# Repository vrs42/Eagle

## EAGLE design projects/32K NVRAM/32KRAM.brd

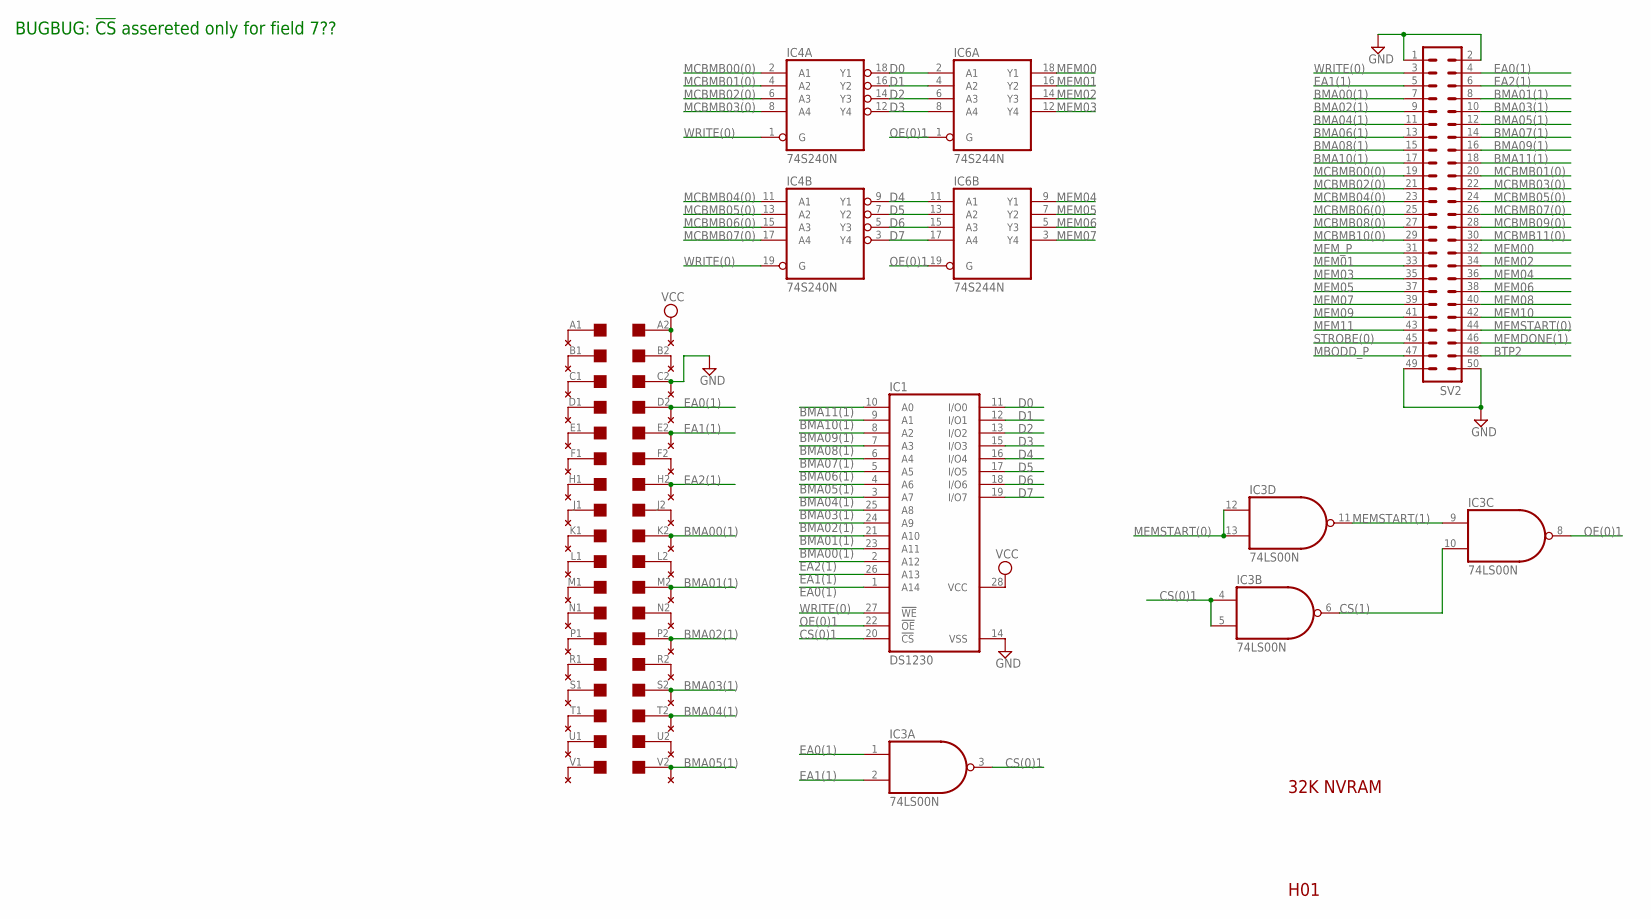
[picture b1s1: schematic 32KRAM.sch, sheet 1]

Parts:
EDGE1: EDGE-CON2
IC1: DS1230; DIL28-6
IC3: 74LS00N; DIL14
IC4: 74S240N; DIL20
IC6: 74S244N; DIL20
SV2: ML50L
U$1: THRU-HOLE2; THRU-HOLEB

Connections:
BMA00(1): EDGE1.K2, IC1.23 (A11), SV2.7, U$1.K2; also elsewhere on the board
BMA01(1): EDGE1.M2, IC1.21 (A10), SV2.8, U$1.M2; also elsewhere on the board
BMA02(1): EDGE1.P2, IC1.24 (A9), SV2.9, U$1.P2; also elsewhere on the board
BMA03(1): EDGE1.S2, IC1.25 (A8), SV2.10, U$1.S2; also elsewhere on the board
BMA04(1): EDGE1.T2, IC1.3 (A7), SV2.11, U$1.T2; also elsewhere on the board
BMA05(1): EDGE1.V2, IC1.4 (A6), SV2.12, U$1.V2; also elsewhere on the board
BMA06(1): IC1.5 (A5), SV2.13; also elsewhere on the board
BMA07(1): IC1.6 (A4), SV2.14; also elsewhere on the board
BMA08(1): IC1.7 (A3), SV2.15; also elsewhere on the board
BMA09(1): IC1.8 (A2), SV2.16; also elsewhere on the board
BMA10(1): IC1.9 (A1), SV2.17; also elsewhere on the board
BMA11(1): IC1.10 (A0), SV2.18; also elsewhere on the board
BTP2: SV2.48; also elsewhere on the board
CS(0)1: IC1.20 (!CS), IC3.3 (O), IC3.4 (I0), IC3.5 (I1)
CS(1): IC3.6 (O), IC3.10 (I1)
D0: IC1.11 (I/O0), IC4.18 (Y1), IC6.2 (A1)
D1: IC1.12 (I/O1), IC4.16 (Y2), IC6.4 (A2)
D2: IC1.13 (I/O2), IC4.14 (Y3), IC6.6 (A3)
D3: IC1.15 (I/O3), IC4.12 (Y4), IC6.8 (A4)
D4: IC1.16 (I/O4), IC4.9 (Y1), IC6.11 (A1)
D5: IC1.17 (I/O5), IC4.7 (Y2), IC6.13 (A2)
D6: IC1.18 (I/O6), IC4.5 (Y3), IC6.15 (A3)
D7: IC1.19 (I/O7), IC4.3 (Y4), IC6.17 (A4)
EA0(1): EDGE1.D2, IC1.1 (A14), IC3.1 (I0), SV2.4, U$1.D2; also elsewhere on the board
EA1(1): EDGE1.E2, IC1.26 (A13), IC3.2 (I1), SV2.5, U$1.E2; also elsewhere on the board
EA2(1): EDGE1.H2, IC1.2 (A12), SV2.6, U$1.H2; also elsewhere on the board
GND: EDGE1.C2, IC1.14 (VSS), IC3.7 (GND), IC4.10 (GND), IC6.10 (GND), SV2.1, SV2.2, SV2.49, SV2.50, U$1.C2; also elsewhere on the board
MBODD_P: SV2.47; also elsewhere on the board
MCBMB00(0): IC4.2 (A1), SV2.19; also elsewhere on the board
MCBMB01(0): IC4.4 (A2), SV2.20; also elsewhere on the board
MCBMB02(0): IC4.6 (A3), SV2.21; also elsewhere on the board
MCBMB03(0): IC4.8 (A4), SV2.22; also elsewhere on the board
MCBMB04(0): IC4.11 (A1), SV2.23; also elsewhere on the board
MCBMB05(0): IC4.13 (A2), SV2.24; also elsewhere on the board
MCBMB06(0): IC4.15 (A3), SV2.25; also elsewhere on the board
MCBMB07(0): IC4.17 (A4), SV2.26; also elsewhere on the board
MCBMB08(0): SV2.27; also elsewhere on the board
MCBMB09(0): SV2.28; also elsewhere on the board
MCBMB10(0): SV2.29; also elsewhere on the board
MCBMB11(0): SV2.30; also elsewhere on the board
MEM00: IC6.18 (Y1), SV2.32; also elsewhere on the board
MEM01: IC6.16 (Y2), SV2.33; also elsewhere on the board
MEM02: IC6.14 (Y3), SV2.34; also elsewhere on the board
MEM03: IC6.12 (Y4), SV2.35; also elsewhere on the board
MEM04: IC6.9 (Y1), SV2.36; also elsewhere on the board
MEM05: IC6.7 (Y2), SV2.37; also elsewhere on the board
MEM06: IC6.5 (Y3), SV2.38; also elsewhere on the board
MEM07: IC6.3 (Y4), SV2.39; also elsewhere on the board
MEM08: SV2.40; also elsewhere on the board
MEM09: SV2.41; also elsewhere on the board
MEM10: SV2.42; also elsewhere on the board
MEM11: SV2.43; also elsewhere on the board
MEMDONE(1): SV2.46; also elsewhere on the board
MEMSTART(0): IC3.12 (I0), IC3.13 (I1), SV2.44; also elsewhere on the board
MEMSTART(1): IC3.9 (I0), IC3.11 (O)
MEM_P: SV2.31; also elsewhere on the board
unnamed: EDGE1.L2, U$1.L2
unnamed: EDGE1.N2, U$1.N2
unnamed: EDGE1.R2, U$1.R2
unnamed: EDGE1.J2, U$1.J2
unnamed: EDGE1.F2, U$1.F2
unnamed: EDGE1.U2, U$1.U2
unnamed: EDGE1.B2, U$1.B2
unnamed: EDGE1.K1, U$1.K1
unnamed: EDGE1.L1, U$1.L1
unnamed: EDGE1.M1, U$1.M1
unnamed: EDGE1.N1, U$1.N1
unnamed: EDGE1.P1, U$1.P1
unnamed: EDGE1.R1, U$1.R1
unnamed: EDGE1.S1, U$1.S1
unnamed: EDGE1.T1, U$1.T1
unnamed: EDGE1.U1, U$1.U1
unnamed: EDGE1.V1, U$1.V1
unnamed: EDGE1.J1, U$1.J1
unnamed: EDGE1.H1, U$1.H1
unnamed: EDGE1.F1, U$1.F1
unnamed: EDGE1.E1, U$1.E1
unnamed: EDGE1.D1, U$1.D1
unnamed: EDGE1.C1, U$1.C1
unnamed: EDGE1.B1, U$1.B1
unnamed: EDGE1.A1, U$1.A1
OE(0)1: IC1.22 (!OE), IC3.8 (O), IC6.1 (G), IC6.19 (G)
STROBE(0): SV2.45; also elsewhere on the board
VCC: EDGE1.A2, IC1.28 (VCC), IC3.14 (VCC), IC4.20 (VCC), IC6.20 (VCC), U$1.A2; also elsewhere on the board
WRITE(0): IC1.27 (!WE), IC4.1 (G), IC4.19 (G), SV2.3; also elsewhere on the board

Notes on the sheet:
32K NVRAM
H01
BUGBUG: !CS! assereted only for field 7??

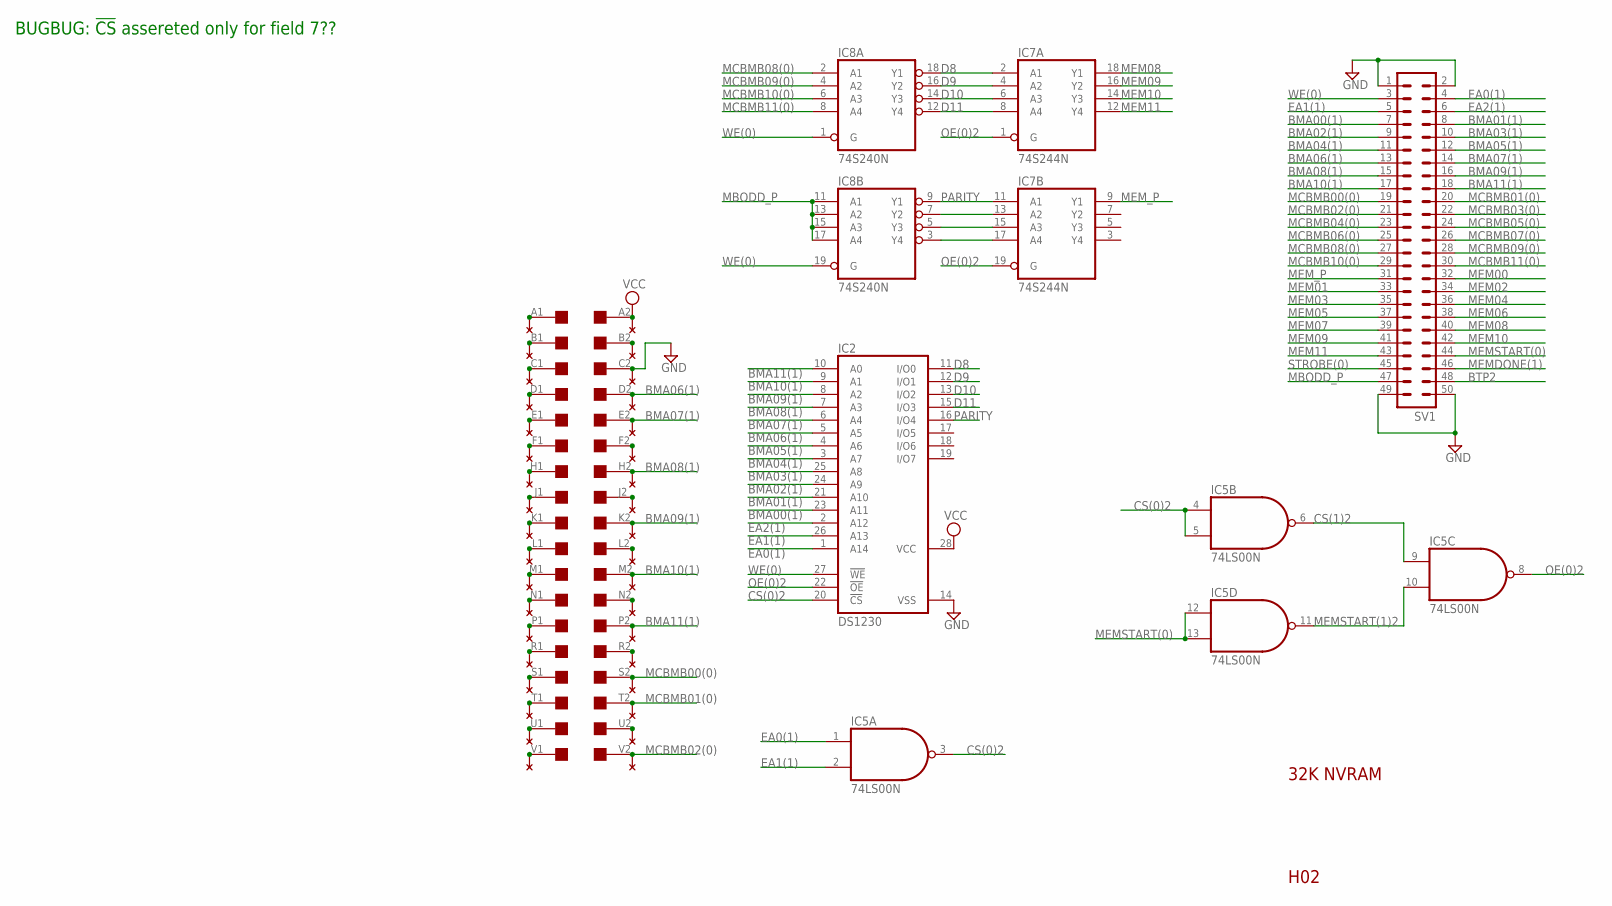
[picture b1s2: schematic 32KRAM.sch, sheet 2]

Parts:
EDGE2: EDGE-CON2
IC2: DS1230; DIL28-6
IC5: 74LS00N; DIL14
IC7: 74S244N; DIL20
IC8: 74S240N; DIL20
SV1: ML50L
U$2: THRU-HOLE2; THRU-HOLEB

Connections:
BMA00(1): IC2.23 (A11), SV1.7; also elsewhere on the board
BMA01(1): IC2.21 (A10), SV1.8; also elsewhere on the board
BMA02(1): IC2.24 (A9), SV1.9; also elsewhere on the board
BMA03(1): IC2.25 (A8), SV1.10; also elsewhere on the board
BMA04(1): IC2.3 (A7), SV1.11; also elsewhere on the board
BMA05(1): IC2.4 (A6), SV1.12; also elsewhere on the board
BMA06(1): EDGE2.D2, IC2.5 (A5), SV1.13, U$2.D2; also elsewhere on the board
BMA07(1): EDGE2.E2, IC2.6 (A4), SV1.14, U$2.E2; also elsewhere on the board
BMA08(1): EDGE2.H2, IC2.7 (A3), SV1.15, U$2.H2; also elsewhere on the board
BMA09(1): EDGE2.K2, IC2.8 (A2), SV1.16, U$2.K2; also elsewhere on the board
BMA10(1): EDGE2.M2, IC2.9 (A1), SV1.17, U$2.M2; also elsewhere on the board
BMA11(1): EDGE2.P2, IC2.10 (A0), SV1.18, U$2.P2; also elsewhere on the board
BTP2: SV1.48; also elsewhere on the board
CS(0)2: IC2.20 (!CS), IC5.3 (O), IC5.4 (I0), IC5.5 (I1)
CS(1)2: IC5.6 (O), IC5.9 (I0)
D8: IC2.11 (I/O0), IC7.2 (A1), IC8.18 (Y1)
D9: IC2.12 (I/O1), IC7.4 (A2), IC8.16 (Y2)
D10: IC2.13 (I/O2), IC7.6 (A3), IC8.14 (Y3)
D11: IC2.15 (I/O3), IC7.8 (A4), IC8.12 (Y4)
EA0(1): IC2.1 (A14), IC5.1 (I0), SV1.4; also elsewhere on the board
EA1(1): IC2.26 (A13), IC5.2 (I1), SV1.5; also elsewhere on the board
EA2(1): IC2.2 (A12), SV1.6; also elsewhere on the board
GND: EDGE2.C2, IC2.14 (VSS), IC5.7 (GND), IC7.10 (GND), IC8.10 (GND), SV1.1, SV1.2, SV1.49, SV1.50, U$2.C2; also elsewhere on the board
MBODD_P: IC8.11 (A1), IC8.13 (A2), IC8.15 (A3), IC8.17 (A4), SV1.47; also elsewhere on the board
MCBMB00(0): EDGE2.S2, SV1.19, U$2.S2; also elsewhere on the board
MCBMB01(0): EDGE2.T2, SV1.20, U$2.T2; also elsewhere on the board
MCBMB02(0): EDGE2.V2, SV1.21, U$2.V2; also elsewhere on the board
MCBMB03(0): SV1.22; also elsewhere on the board
MCBMB04(0): SV1.23; also elsewhere on the board
MCBMB05(0): SV1.24; also elsewhere on the board
MCBMB06(0): SV1.25; also elsewhere on the board
MCBMB07(0): SV1.26; also elsewhere on the board
MCBMB08(0): IC8.2 (A1), SV1.27; also elsewhere on the board
MCBMB09(0): IC8.4 (A2), SV1.28; also elsewhere on the board
MCBMB10(0): IC8.6 (A3), SV1.29; also elsewhere on the board
MCBMB11(0): IC8.8 (A4), SV1.30; also elsewhere on the board
MEM00: SV1.32; also elsewhere on the board
MEM01: SV1.33; also elsewhere on the board
MEM02: SV1.34; also elsewhere on the board
MEM03: SV1.35; also elsewhere on the board
MEM04: SV1.36; also elsewhere on the board
MEM05: SV1.37; also elsewhere on the board
MEM06: SV1.38; also elsewhere on the board
MEM07: SV1.39; also elsewhere on the board
MEM08: IC7.18 (Y1), SV1.40; also elsewhere on the board
MEM09: IC7.16 (Y2), SV1.41; also elsewhere on the board
MEM10: IC7.14 (Y3), SV1.42; also elsewhere on the board
MEM11: IC7.12 (Y4), SV1.43; also elsewhere on the board
MEMDONE(1): SV1.46; also elsewhere on the board
MEMSTART(0): IC5.12 (I0), IC5.13 (I1), SV1.44; also elsewhere on the board
MEMSTART(1)2: IC5.10 (I1), IC5.11 (O)
MEM_P: IC7.9 (Y1), SV1.31; also elsewhere on the board
unnamed: IC7.13 (A2), IC8.7 (Y2)
unnamed: IC7.15 (A3), IC8.5 (Y3)
unnamed: IC7.17 (A4), IC8.3 (Y4)
unnamed: EDGE2.L2, U$2.L2
unnamed: EDGE2.N2, U$2.N2
unnamed: EDGE2.R2, U$2.R2
unnamed: EDGE2.J2, U$2.J2
unnamed: EDGE2.F2, U$2.F2
unnamed: EDGE2.U2, U$2.U2
unnamed: EDGE2.B2, U$2.B2
unnamed: EDGE2.K1, U$2.K1
unnamed: EDGE2.L1, U$2.L1
unnamed: EDGE2.M1, U$2.M1
unnamed: EDGE2.N1, U$2.N1
unnamed: EDGE2.P1, U$2.P1
unnamed: EDGE2.R1, U$2.R1
unnamed: EDGE2.S1, U$2.S1
unnamed: EDGE2.T1, U$2.T1
unnamed: EDGE2.U1, U$2.U1
unnamed: EDGE2.V1, U$2.V1
unnamed: EDGE2.J1, U$2.J1
unnamed: EDGE2.H1, U$2.H1
unnamed: EDGE2.F1, U$2.F1
unnamed: EDGE2.E1, U$2.E1
unnamed: EDGE2.D1, U$2.D1
unnamed: EDGE2.C1, U$2.C1
unnamed: EDGE2.B1, U$2.B1
unnamed: EDGE2.A1, U$2.A1
OE(0)2: IC2.22 (!OE), IC5.8 (O), IC7.1 (G), IC7.19 (G)
PARITY: IC2.16 (I/O4), IC7.11 (A1), IC8.9 (Y1)
STROBE(0): SV1.45; also elsewhere on the board
VCC: EDGE2.A2, IC2.28 (VCC), IC5.14 (VCC), IC7.20 (VCC), IC8.20 (VCC), U$2.A2; also elsewhere on the board
WE(0): IC2.27 (!WE), IC8.1 (G), IC8.19 (G), SV1.3; also elsewhere on the board

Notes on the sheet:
32K NVRAM
H02
BUGBUG: !CS! assereted only for field 7??

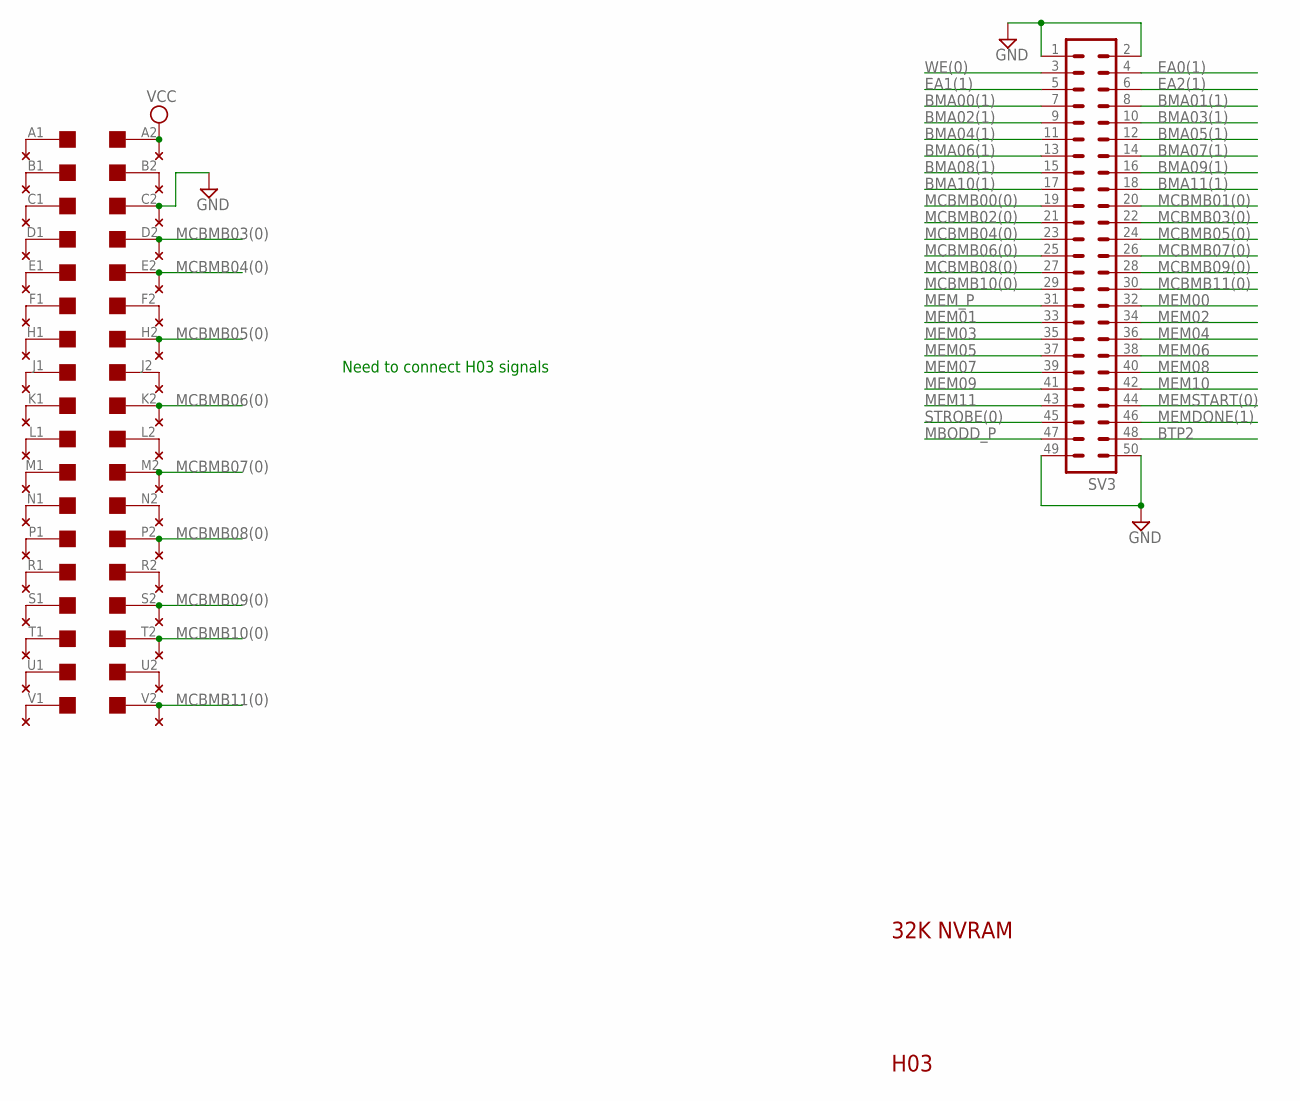
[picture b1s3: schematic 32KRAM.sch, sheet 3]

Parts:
EDGE3: EDGE-CON2
SV3: ML50L
U$3: THRU-HOLE2; THRU-HOLEB

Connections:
BMA00(1): SV3.7; also elsewhere on the board
BMA01(1): SV3.8; also elsewhere on the board
BMA02(1): SV3.9; also elsewhere on the board
BMA03(1): SV3.10; also elsewhere on the board
BMA04(1): SV3.11; also elsewhere on the board
BMA05(1): SV3.12; also elsewhere on the board
BMA06(1): SV3.13; also elsewhere on the board
BMA07(1): SV3.14; also elsewhere on the board
BMA08(1): SV3.15; also elsewhere on the board
BMA09(1): SV3.16; also elsewhere on the board
BMA10(1): SV3.17; also elsewhere on the board
BMA11(1): SV3.18; also elsewhere on the board
BTP2: SV3.48; also elsewhere on the board
EA0(1): SV3.4; also elsewhere on the board
EA1(1): SV3.5; also elsewhere on the board
EA2(1): SV3.6; also elsewhere on the board
GND: EDGE3.C2, SV3.1, SV3.2, SV3.49, SV3.50, U$3.C2; also elsewhere on the board
MBODD_P: SV3.47; also elsewhere on the board
MCBMB00(0): SV3.19; also elsewhere on the board
MCBMB01(0): SV3.20; also elsewhere on the board
MCBMB02(0): SV3.21; also elsewhere on the board
MCBMB03(0): EDGE3.D2, SV3.22, U$3.D2; also elsewhere on the board
MCBMB04(0): EDGE3.E2, SV3.23, U$3.E2; also elsewhere on the board
MCBMB05(0): EDGE3.H2, SV3.24, U$3.H2; also elsewhere on the board
MCBMB06(0): EDGE3.K2, SV3.25, U$3.K2; also elsewhere on the board
MCBMB07(0): EDGE3.M2, SV3.26, U$3.M2; also elsewhere on the board
MCBMB08(0): EDGE3.P2, SV3.27, U$3.P2; also elsewhere on the board
MCBMB09(0): EDGE3.S2, SV3.28, U$3.S2; also elsewhere on the board
MCBMB10(0): EDGE3.T2, SV3.29, U$3.T2; also elsewhere on the board
MCBMB11(0): EDGE3.V2, SV3.30, U$3.V2; also elsewhere on the board
MEM00: SV3.32; also elsewhere on the board
MEM01: SV3.33; also elsewhere on the board
MEM02: SV3.34; also elsewhere on the board
MEM03: SV3.35; also elsewhere on the board
MEM04: SV3.36; also elsewhere on the board
MEM05: SV3.37; also elsewhere on the board
MEM06: SV3.38; also elsewhere on the board
MEM07: SV3.39; also elsewhere on the board
MEM08: SV3.40; also elsewhere on the board
MEM09: SV3.41; also elsewhere on the board
MEM10: SV3.42; also elsewhere on the board
MEM11: SV3.43; also elsewhere on the board
MEMDONE(1): SV3.46; also elsewhere on the board
MEMSTART(0): SV3.44; also elsewhere on the board
MEM_P: SV3.31; also elsewhere on the board
unnamed: EDGE3.J2, U$3.J2
unnamed: EDGE3.L2, U$3.L2
unnamed: EDGE3.N2, U$3.N2
unnamed: EDGE3.F2, U$3.F2
unnamed: EDGE3.R2, U$3.R2
unnamed: EDGE3.B2, U$3.B2
unnamed: EDGE3.U2, U$3.U2
unnamed: EDGE3.A1, U$3.A1
unnamed: EDGE3.V1, U$3.V1
unnamed: EDGE3.U1, U$3.U1
unnamed: EDGE3.T1, U$3.T1
unnamed: EDGE3.S1, U$3.S1
unnamed: EDGE3.R1, U$3.R1
unnamed: EDGE3.P1, U$3.P1
unnamed: EDGE3.N1, U$3.N1
unnamed: EDGE3.M1, U$3.M1
unnamed: EDGE3.L1, U$3.L1
unnamed: EDGE3.K1, U$3.K1
unnamed: EDGE3.J1, U$3.J1
unnamed: EDGE3.H1, U$3.H1
unnamed: EDGE3.F1, U$3.F1
unnamed: EDGE3.E1, U$3.E1
unnamed: EDGE3.D1, U$3.D1
unnamed: EDGE3.C1, U$3.C1
unnamed: EDGE3.B1, U$3.B1
STROBE(0): SV3.45; also elsewhere on the board
VCC: EDGE3.A2, U$3.A2; also elsewhere on the board
WE(0): SV3.3; also elsewhere on the board

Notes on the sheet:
32K NVRAM
H03
Need to connect H03 signals

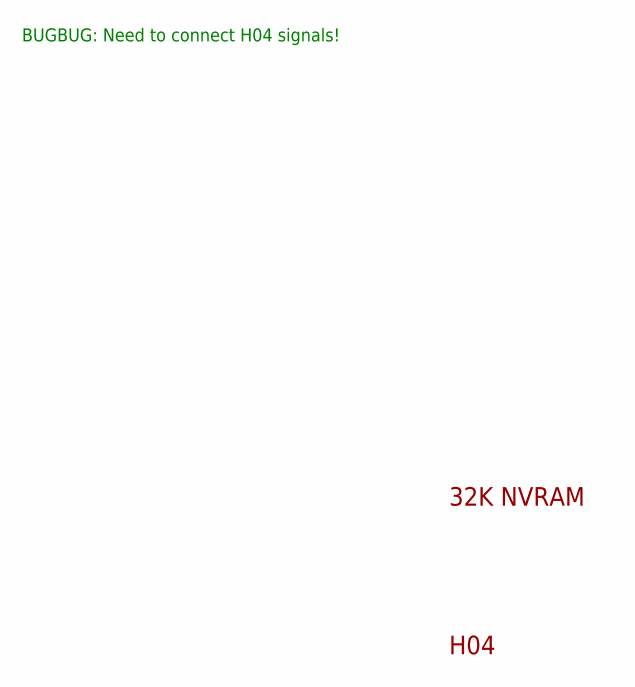
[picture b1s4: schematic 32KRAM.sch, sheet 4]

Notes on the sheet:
32K NVRAM
H04
BUGBUG: Need to connect H04 signals!

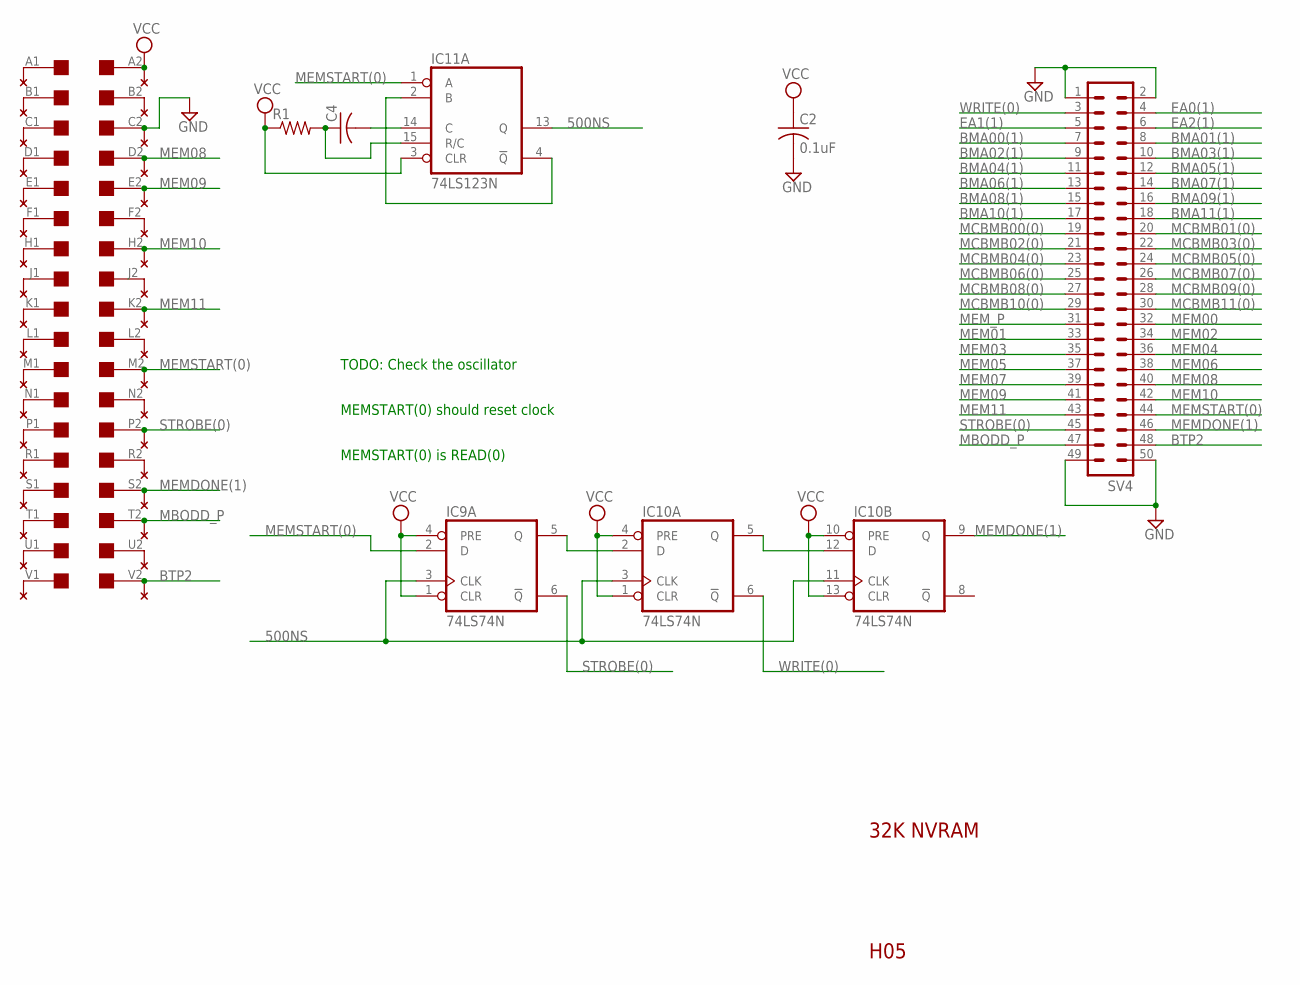
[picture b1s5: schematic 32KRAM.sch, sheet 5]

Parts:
C2: 0.1uF; C050-025X075
C4: C-US050-025X075; C050-025X075
EDGE5: EDGE-CON2
IC9, IC10: 74LS74N; DIL14
IC11: 74LS123N; DIL16
R1: R-US_0309/10; 0309/10
SV4: ML50L
U$5: THRU-HOLE2; THRU-HOLEB

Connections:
500NS: IC9.3 (CLK), IC10.3 (CLK), IC10.11 (CLK), IC11.13 (Q)
BMA00(1): SV4.7; also elsewhere on the board
BMA01(1): SV4.8; also elsewhere on the board
BMA02(1): SV4.9; also elsewhere on the board
BMA03(1): SV4.10; also elsewhere on the board
BMA04(1): SV4.11; also elsewhere on the board
BMA05(1): SV4.12; also elsewhere on the board
BMA06(1): SV4.13; also elsewhere on the board
BMA07(1): SV4.14; also elsewhere on the board
BMA08(1): SV4.15; also elsewhere on the board
BMA09(1): SV4.16; also elsewhere on the board
BMA10(1): SV4.17; also elsewhere on the board
BMA11(1): SV4.18; also elsewhere on the board
BTP2: EDGE5.V2, SV4.48, U$5.V2; also elsewhere on the board
EA0(1): SV4.4; also elsewhere on the board
EA1(1): SV4.5; also elsewhere on the board
EA2(1): SV4.6; also elsewhere on the board
GND: C2.2, EDGE5.C2, IC9.7 (GND), IC10.7 (GND), IC11.8 (GND), SV4.1, SV4.2, SV4.49, SV4.50, U$5.C2; also elsewhere on the board
MBODD_P: EDGE5.T2, SV4.47, U$5.T2; also elsewhere on the board
MCBMB00(0): SV4.19; also elsewhere on the board
MCBMB01(0): SV4.20; also elsewhere on the board
MCBMB02(0): SV4.21; also elsewhere on the board
MCBMB03(0): SV4.22; also elsewhere on the board
MCBMB04(0): SV4.23; also elsewhere on the board
MCBMB05(0): SV4.24; also elsewhere on the board
MCBMB06(0): SV4.25; also elsewhere on the board
MCBMB07(0): SV4.26; also elsewhere on the board
MCBMB08(0): SV4.27; also elsewhere on the board
MCBMB09(0): SV4.28; also elsewhere on the board
MCBMB10(0): SV4.29; also elsewhere on the board
MCBMB11(0): SV4.30; also elsewhere on the board
MEM00: SV4.32; also elsewhere on the board
MEM01: SV4.33; also elsewhere on the board
MEM02: SV4.34; also elsewhere on the board
MEM03: SV4.35; also elsewhere on the board
MEM04: SV4.36; also elsewhere on the board
MEM05: SV4.37; also elsewhere on the board
MEM06: SV4.38; also elsewhere on the board
MEM07: SV4.39; also elsewhere on the board
MEM08: EDGE5.D2, SV4.40, U$5.D2; also elsewhere on the board
MEM09: EDGE5.E2, SV4.41, U$5.E2; also elsewhere on the board
MEM10: EDGE5.H2, SV4.42, U$5.H2; also elsewhere on the board
MEM11: EDGE5.K2, SV4.43, U$5.K2; also elsewhere on the board
MEMDONE(1): EDGE5.S2, IC10.9 (Q), SV4.46, U$5.S2; also elsewhere on the board
MEMSTART(0): EDGE5.M2, IC9.2 (D), IC11.1 (A), SV4.44, U$5.M2; also elsewhere on the board
MEM_P: SV4.31; also elsewhere on the board
unnamed: IC9.5 (Q), IC10.2 (D)
unnamed: IC10.5 (Q), IC10.12 (D)
unnamed: IC11.2 (B), IC11.4 (!Q)
unnamed: C4.2, IC11.14 (C)
unnamed: C4.1, IC11.15 (R/C), R1.2
unnamed: EDGE5.J2, U$5.J2
unnamed: EDGE5.L2, U$5.L2
unnamed: EDGE5.N2, U$5.N2
unnamed: EDGE5.F2, U$5.F2
unnamed: EDGE5.R2, U$5.R2
unnamed: EDGE5.B2, U$5.B2
unnamed: EDGE5.U2, U$5.U2
unnamed: EDGE5.A1, U$5.A1
unnamed: EDGE5.V1, U$5.V1
unnamed: EDGE5.U1, U$5.U1
unnamed: EDGE5.T1, U$5.T1
unnamed: EDGE5.S1, U$5.S1
unnamed: EDGE5.R1, U$5.R1
unnamed: EDGE5.P1, U$5.P1
unnamed: EDGE5.N1, U$5.N1
unnamed: EDGE5.M1, U$5.M1
unnamed: EDGE5.L1, U$5.L1
unnamed: EDGE5.K1, U$5.K1
unnamed: EDGE5.J1, U$5.J1
unnamed: EDGE5.H1, U$5.H1
unnamed: EDGE5.F1, U$5.F1
unnamed: EDGE5.E1, U$5.E1
unnamed: EDGE5.D1, U$5.D1
unnamed: EDGE5.C1, U$5.C1
unnamed: EDGE5.B1, U$5.B1
STROBE(0): EDGE5.P2, IC9.6 (!Q), SV4.45, U$5.P2; also elsewhere on the board
VCC: C2.1, EDGE5.A2, IC9.1 (CLR), IC9.4 (PRE), IC9.14 (VCC), IC10.1 (CLR), IC10.4 (PRE), IC10.10 (PRE), IC10.13 (CLR), IC10.14 (VCC), IC11.3 (CLR), IC11.16 (VCC), R1.1, U$5.A2; also elsewhere on the board
WRITE(0): IC10.6 (!Q), SV4.3; also elsewhere on the board

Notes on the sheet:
32K NVRAM
H05
TODO: Check the oscillator
MEMSTART(0) is READ(0)
MEMSTART(0) should reset clock

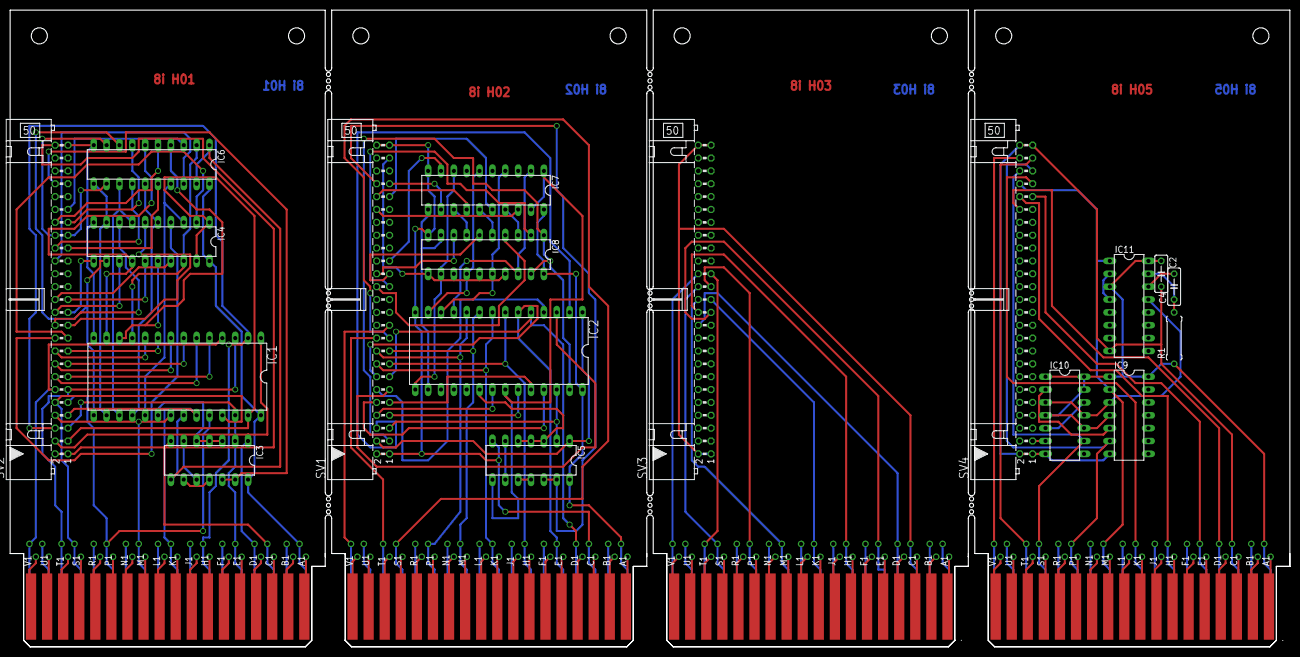
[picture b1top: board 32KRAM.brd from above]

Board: 2 copper layers, 252.7 x 125.7 mm, 27 parts (0 on the bottom side), 179 nets.

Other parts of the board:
E$1: DECPROTO1111

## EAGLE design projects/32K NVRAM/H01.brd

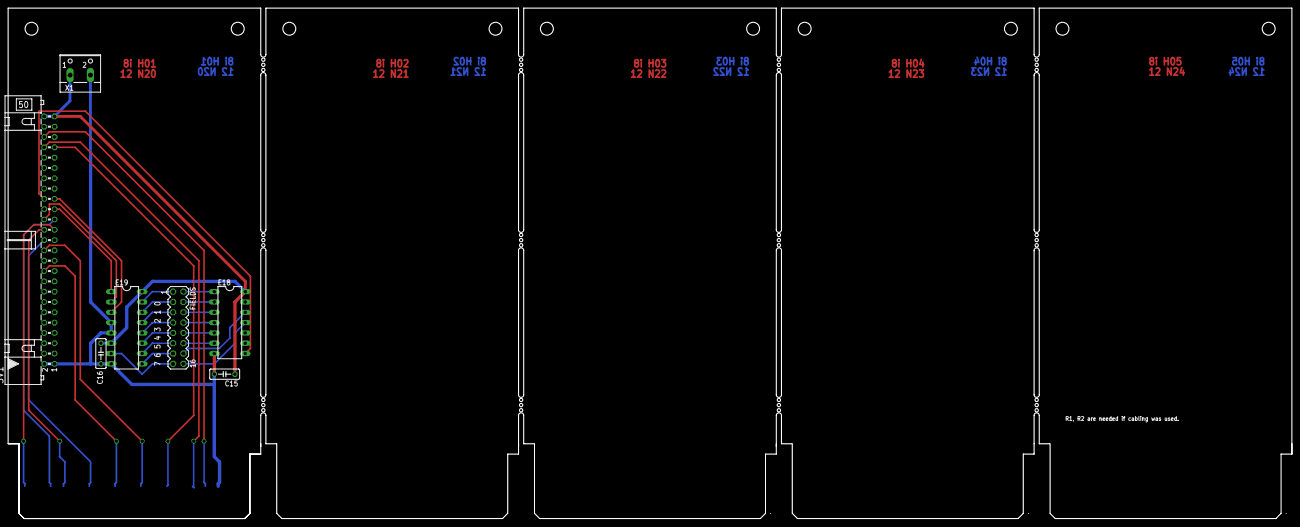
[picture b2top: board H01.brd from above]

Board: 2 copper layers, 316.2 x 125.7 mm, 9 parts (0 on the bottom side), 31 nets.

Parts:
C15, C16: 0.1uF; C050-025X075
E18: 74LS30N; DIL14
E19: 74LS138N; DIL16
FIELDS: MA08-2
H01: EDGE-CON1
SV1: ML50L
U$6: DECPROTO11111
X1: POWER; W237-102

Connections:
BMA00(1): H01.K2, SV1.24
BMA01(1): H01.M2, SV1.20
BMA02(1): H01.P2, SV1.26
BMA03(1): H01.S2, SV1.28
BMA04(1): H01.T2, SV1.29
BMA05(1): H01.V2, SV1.27
EA0(1): E19.3, SV1.33
EA1(1): E19.2, SV1.30
EA2(1): E19.1, SV1.31
FS(1): E18.8, SV1.34
GND: C15.2, C16.2, E18.7, E19.4, E19.5, E19.8, H01.C2, SV1.1, SV1.2, X1.2
MCBMB03(0): H01.D2, SV1.46
MCBMB04(0): H01.E2, SV1.44
MCBMB05(0): H01.H2, SV1.43
unnamed: E19.15, FIELDS.1
unnamed: E19.14, FIELDS.3
unnamed: E19.13, FIELDS.5
unnamed: E19.12, FIELDS.7
unnamed: E19.11, FIELDS.9
unnamed: E19.10, FIELDS.11
unnamed: E19.9, FIELDS.13
unnamed: E19.7, FIELDS.15
unnamed: E18.4, FIELDS.8
unnamed: E18.3, FIELDS.6
unnamed: E18.2, FIELDS.4
unnamed: E18.1, FIELDS.2
unnamed: E18.5, FIELDS.10
unnamed: E18.6, FIELDS.12
unnamed: E18.12, FIELDS.14
unnamed: E18.11, FIELDS.16
VCC: C15.1, C16.1, E18.14, E19.6, E19.16, SV1.49, SV1.50, X1.1

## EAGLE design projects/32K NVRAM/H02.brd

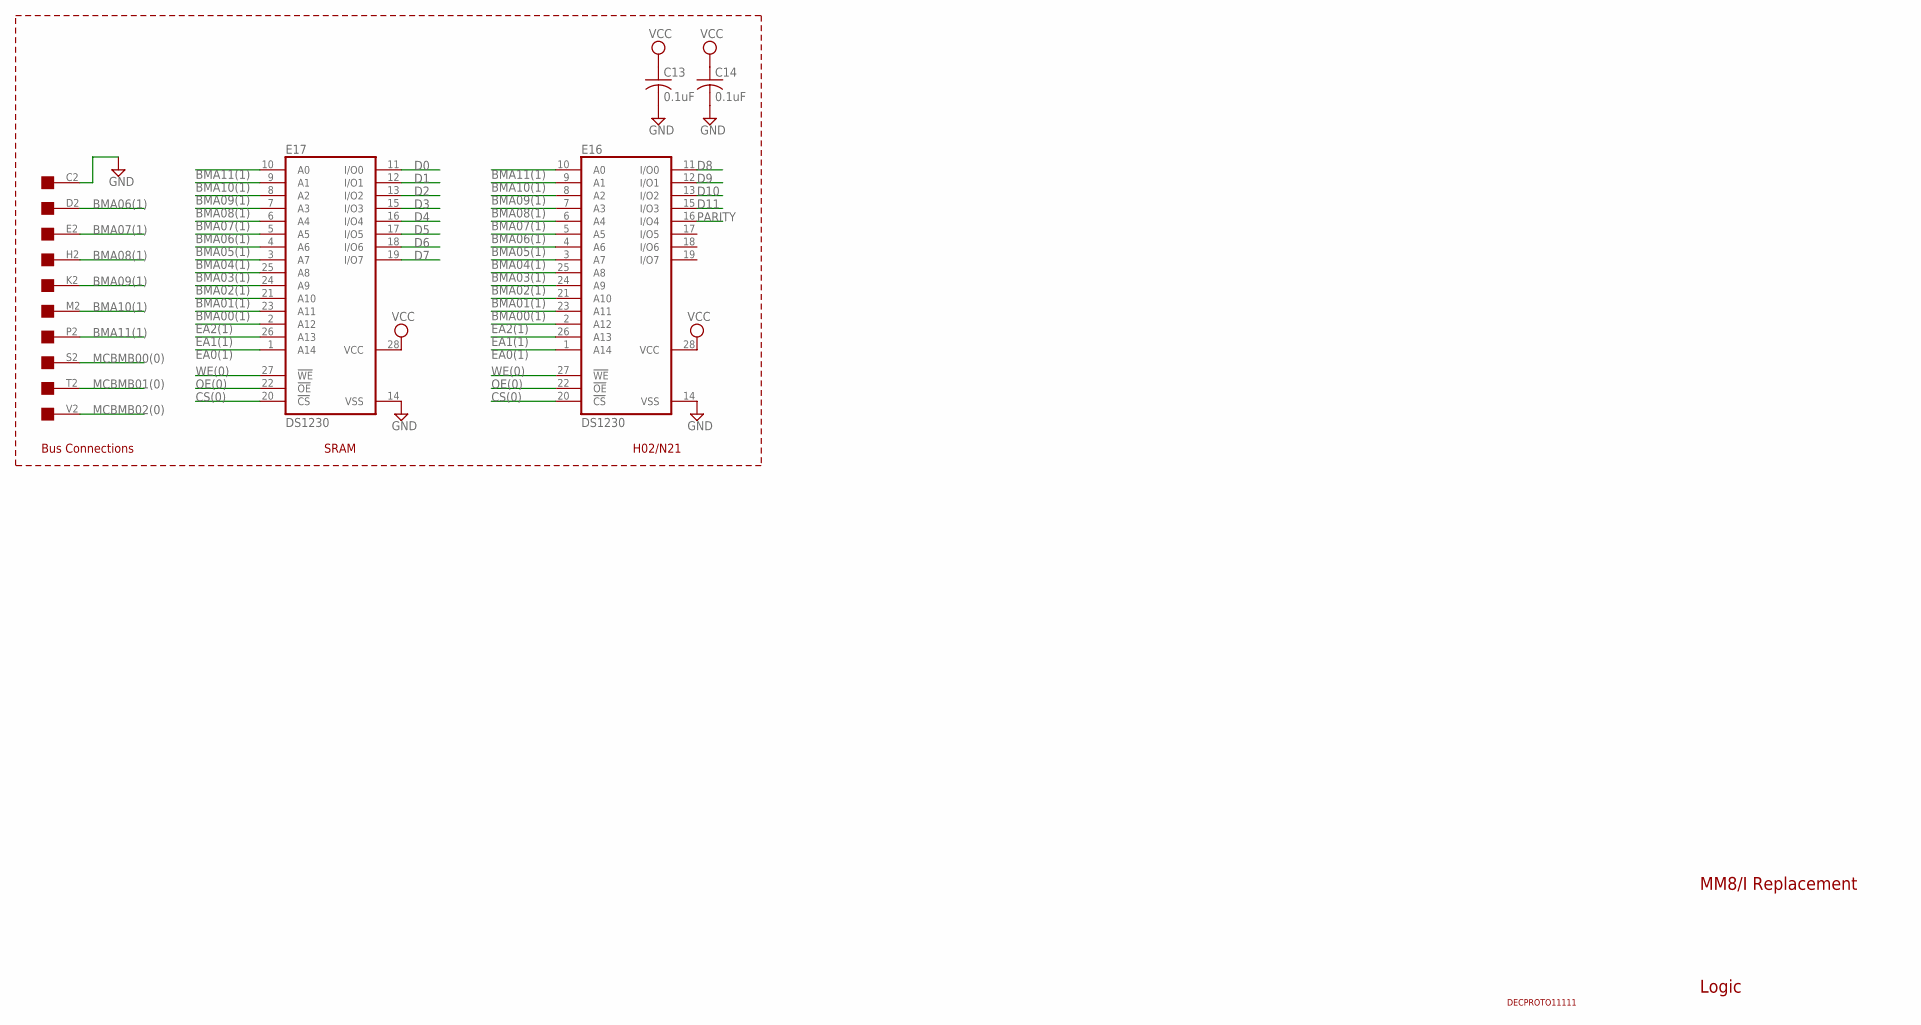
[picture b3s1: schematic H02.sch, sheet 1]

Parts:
C13, C14: 0.1uF; C050-025X075
E16, E17: DS1230; DIL28-6
H02: EDGE-CON1
U$6: DECPROTO11111

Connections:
BMA00(1): E16.23 (A11), E17.23 (A11); also elsewhere on the board
BMA01(1): E16.21 (A10), E17.21 (A10); also elsewhere on the board
BMA02(1): E16.24 (A9), E17.24 (A9); also elsewhere on the board
BMA03(1): E16.25 (A8), E17.25 (A8); also elsewhere on the board
BMA04(1): E16.3 (A7), E17.3 (A7); also elsewhere on the board
BMA05(1): E16.4 (A6), E17.4 (A6); also elsewhere on the board
BMA06(1): E16.5 (A5), E17.5 (A5), H02.D2; also elsewhere on the board
BMA07(1): E16.6 (A4), E17.6 (A4), H02.E2; also elsewhere on the board
BMA08(1): E16.7 (A3), E17.7 (A3), H02.H2; also elsewhere on the board
BMA09(1): E16.8 (A2), E17.8 (A2), H02.K2; also elsewhere on the board
BMA10(1): E16.9 (A1), E17.9 (A1), H02.M2; also elsewhere on the board
BMA11(1): E16.10 (A0), E17.10 (A0), H02.P2; also elsewhere on the board
CS(0): E16.20 (!CS), E17.20 (!CS); also elsewhere on the board
D0: E17.11 (I/O0); also elsewhere on the board
D1: E17.12 (I/O1); also elsewhere on the board
D2: E17.13 (I/O2); also elsewhere on the board
D3: E17.15 (I/O3); also elsewhere on the board
D4: E17.16 (I/O4); also elsewhere on the board
D5: E17.17 (I/O5); also elsewhere on the board
D6: E17.18 (I/O6); also elsewhere on the board
D7: E17.19 (I/O7); also elsewhere on the board
D8: E16.11 (I/O0); also elsewhere on the board
D9: E16.12 (I/O1); also elsewhere on the board
D10: E16.13 (I/O2); also elsewhere on the board
D11: E16.15 (I/O3); also elsewhere on the board
EA0(1): E16.1 (A14), E17.1 (A14); also elsewhere on the board
EA1(1): E16.26 (A13), E17.26 (A13); also elsewhere on the board
EA2(1): E16.2 (A12), E17.2 (A12); also elsewhere on the board
GND: C13.2, C14.2, E16.14 (VSS), E17.14 (VSS), H02.C2; also elsewhere on the board
MCBMB00(0): H02.S2; also elsewhere on the board
MCBMB01(0): H02.T2; also elsewhere on the board
MCBMB02(0): H02.V2; also elsewhere on the board
OE(0): E16.22 (!OE), E17.22 (!OE); also elsewhere on the board
PARITY: E16.16 (I/O4); also elsewhere on the board
VCC: C13.1, C14.1, E16.28 (VCC), E17.28 (VCC); also elsewhere on the board
WE(0): E16.27 (!WE), E17.27 (!WE); also elsewhere on the board

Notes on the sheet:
H02/N21
SRAM
MM8/I Replacement
Logic
Bus Connections

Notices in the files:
parts and their libraries:
SparkFun-Hardware: Licensing: Creative Commons ShareAlike 4.0 International - https://creativecommons.org/licenses/by-sa/4.0
